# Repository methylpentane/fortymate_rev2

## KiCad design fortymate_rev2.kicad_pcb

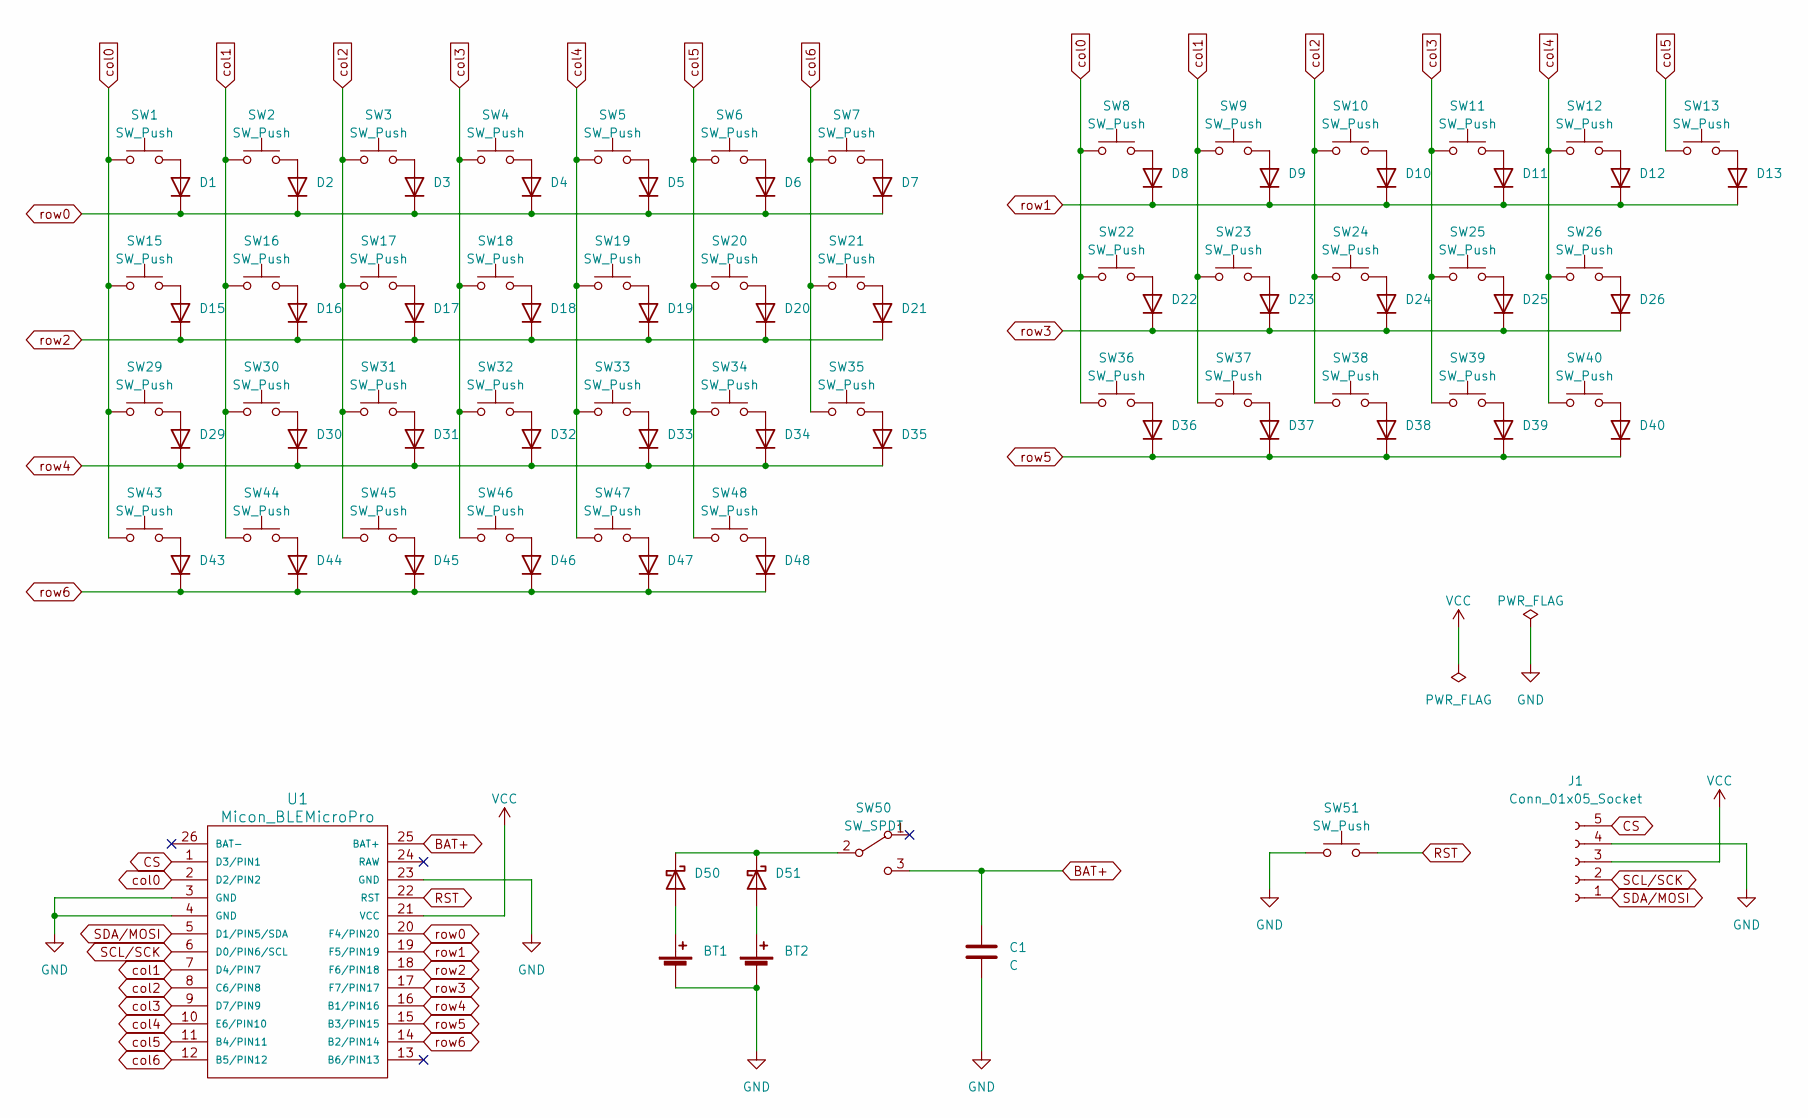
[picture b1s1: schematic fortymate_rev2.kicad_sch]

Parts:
BT1, BT2: Battery_Cell; Battery_ali_CR1632
C1: C; C_1206_3216Metric
D1, D2, D3, D4, D5, D6, D7, D8, D9, D10, D11, D12, D13, D15, D16, D17, D18, D19, D20, D21, D22, D23, D24, D25, D26, D29, D30, D31, D32, D33, D34, D35, D36, D37, D38, D39, D40, D43, D44, D45, D46, D47, D48: diode; Diode_SMD
D50, D51: D_Schottky; Diode_SMD
J1: Conn_01x05_Socket; PinSocket_1x05_P2.54mm_Vertical
SW1, SW2, SW3, SW4, SW5, SW6, SW7, SW8, SW9, SW10, SW11, SW12, SW13, SW15, SW16, SW17, SW18, SW19, SW20, SW21, SW22, SW23, SW24, SW25, SW26, SW29, SW30, SW31, SW32, SW33, SW34, SW35, SW36, SW37, SW38, SW39, SW40, SW43, SW44, SW45, SW46, SW47, SW48: SW_Push; CherryMX_Hotswap_1u
SW50: SW_SPDT; TGSW_MK12C02
SW51: SW_Push; ResetSW
U1: Micon_BLEMicroPro; Micon_BMP_7sKB

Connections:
BAT+: C1.1, SW50.3 (C), U1.25 (BAT+)
CS: J1.5, U1.1 (D3/PIN1)
GND: BT1.2 (-), BT2.2 (-), C1.2, J1.4, SW51.1, U1.3 (GND), U1.4 (GND), U1.23 (GND); also elsewhere on the board
unnamed: BT1.1 (+), D50.2 (A)
unnamed: BT2.1 (+), D51.2 (A)
unnamed: D1.2 (A), SW1.2
unnamed: D2.2 (A), SW2.2
unnamed: D3.2 (A), SW3.2
unnamed: D4.2 (A), SW4.2
unnamed: D5.2 (A), SW5.2
unnamed: D6.2 (A), SW6.2
unnamed: D7.2 (A), SW7.2
unnamed: D8.2 (A), SW8.2
unnamed: D9.2 (A), SW9.2
unnamed: D10.2 (A), SW10.2
unnamed: D11.2 (A), SW11.2
unnamed: D12.2 (A), SW12.2
unnamed: D13.2 (A), SW13.2
unnamed: D15.2 (A), SW15.2
unnamed: D16.2 (A), SW16.2
unnamed: D17.2 (A), SW17.2
unnamed: D18.2 (A), SW18.2
unnamed: D19.2 (A), SW19.2
unnamed: D20.2 (A), SW20.2
unnamed: D21.2 (A), SW21.2
unnamed: D22.2 (A), SW22.2
unnamed: D23.2 (A), SW23.2
unnamed: D24.2 (A), SW24.2
unnamed: D25.2 (A), SW25.2
unnamed: D26.2 (A), SW26.2
unnamed: D29.2 (A), SW29.2
unnamed: D30.2 (A), SW30.2
unnamed: D31.2 (A), SW31.2
unnamed: D32.2 (A), SW32.2
unnamed: D33.2 (A), SW33.2
unnamed: D34.2 (A), SW34.2
unnamed: D35.2 (A), SW35.2
unnamed: D36.2 (A), SW36.2
unnamed: D37.2 (A), SW37.2
unnamed: D38.2 (A), SW38.2
unnamed: D39.2 (A), SW39.2
unnamed: D40.2 (A), SW40.2
unnamed: D43.2 (A), SW43.2
unnamed: D44.2 (A), SW44.2
unnamed: D45.2 (A), SW45.2
unnamed: D46.2 (A), SW46.2
unnamed: D47.2 (A), SW47.2
unnamed: D48.2 (A), SW48.2
unnamed: D50.1 (K), D51.1 (K), SW50.2 (B)
RST: SW51.2, U1.22 (RST); also elsewhere on the board
SCL/SCK: J1.2, U1.6 (D0/PIN6/SCL)
SDA/MOSI: J1.1, U1.5 (D1/PIN5/SDA)
VCC: J1.3, U1.21 (VCC)
col0: SW1.1, SW8.1, SW15.1, SW22.1, SW29.1, SW36.1, SW43.1, U1.2 (D2/PIN2)
col1: SW2.1, SW9.1, SW16.1, SW23.1, SW30.1, SW37.1, SW44.1, U1.7 (D4/PIN7)
col2: SW3.1, SW10.1, SW17.1, SW24.1, SW31.1, SW38.1, SW45.1, U1.8 (C6/PIN8)
col3: SW4.1, SW11.1, SW18.1, SW25.1, SW32.1, SW39.1, SW46.1, U1.9 (D7/PIN9)
col4: SW5.1, SW12.1, SW19.1, SW26.1, SW33.1, SW40.1, SW47.1, U1.10 (E6/PIN10)
col5: SW6.1, SW13.1, SW20.1, SW34.1, SW48.1, U1.11 (B4/PIN11)
col6: SW7.1, SW21.1, SW35.1, U1.12 (B5/PIN12)
row0: D1.1 (K), D2.1 (K), D3.1 (K), D4.1 (K), D5.1 (K), D6.1 (K), D7.1 (K), U1.20 (F4/PIN20)
row1: D8.1 (K), D9.1 (K), D10.1 (K), D11.1 (K), D12.1 (K), D13.1 (K), U1.19 (F5/PIN19)
row2: D15.1 (K), D16.1 (K), D17.1 (K), D18.1 (K), D19.1 (K), D20.1 (K), D21.1 (K), U1.18 (F6/PIN18)
row3: D22.1 (K), D23.1 (K), D24.1 (K), D25.1 (K), D26.1 (K), U1.17 (F7/PIN17)
row4: D29.1 (K), D30.1 (K), D31.1 (K), D32.1 (K), D33.1 (K), D34.1 (K), D35.1 (K), U1.16 (B1/PIN16)
row5: D36.1 (K), D37.1 (K), D38.1 (K), D39.1 (K), D40.1 (K), U1.15 (B3/PIN15)
row6: D43.1 (K), D44.1 (K), D45.1 (K), D46.1 (K), D47.1 (K), D48.1 (K), U1.14 (B2/PIN14)

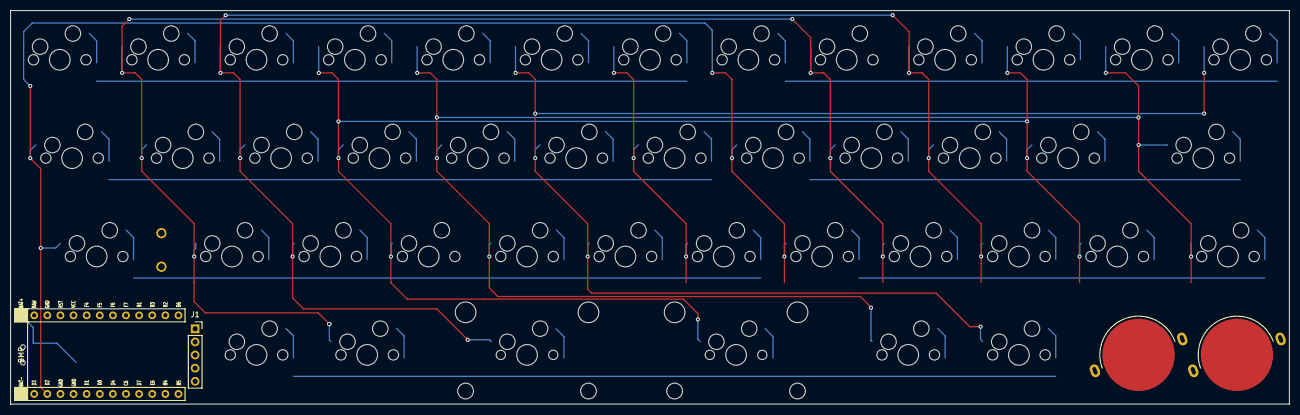
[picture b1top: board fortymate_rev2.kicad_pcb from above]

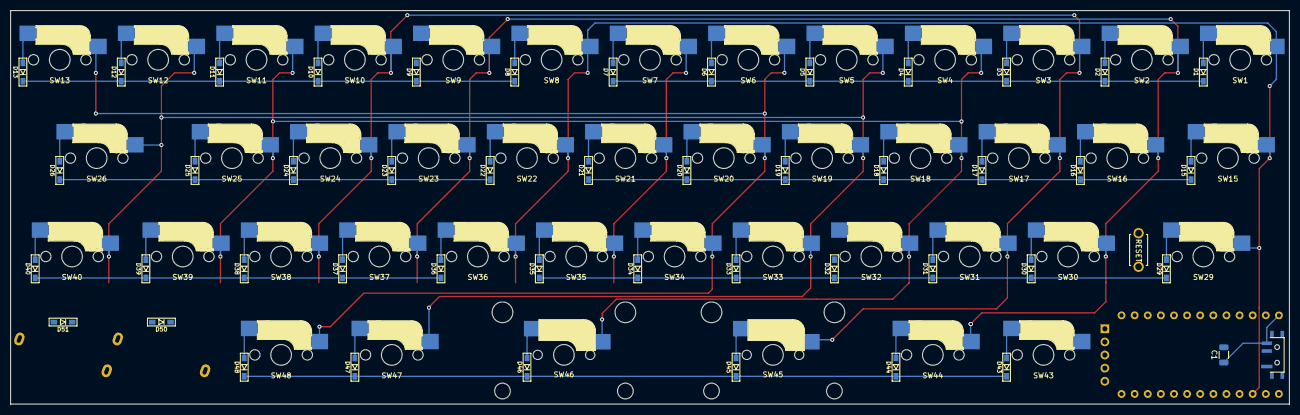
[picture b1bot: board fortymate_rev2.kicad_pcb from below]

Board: 2 copper layers, 247.7 x 76.2 mm, 95 parts (2 on the bottom side), 67 nets.

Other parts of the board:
SWe: SW_Push; ResetSW

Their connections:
GND: SWe.1; also elsewhere on the board
RST: SWe.2; also elsewhere on the board

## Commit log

2023-04-09 gitignore
2024-02-24 PCB WIP
2024-03-13 PCB progress + submodulized salicylic lib
2024-03-15 more pcb progress
